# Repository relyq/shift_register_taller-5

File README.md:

# shift_register_taller-5

esquematica y diseño de pcb del proyecto de shift register de 5º año 2018<br>
./CAMOutputs/ - gerber shift register
./CAMOutputs-control/ - gerber control
./shift_register/ - directorio del proyecto de eagle con los .sch y .brd<br>
./docs/ - directorio con las datasheets<br>

el proyecto incluye un control para conectar a las entradas de un lado de la pcb y así controlar los registros sin necesidad de pulsadores en una protoboard

<h1>PDF</h1>
./shift_register.pdf - diseño de pcb principal<br>
./shift_register-control.pdf - diseño de pcb del control<br>
./shift_register-components.pdf - pcb principal lado componentes<br>
./shift_register-control-components.pdf - pcb del control lado componentes<br>
./shift_register-schematic.pdf - esquematica<br>
<br>
./shiftreg_imprimir.pdf - hoja con 4 copias de cada diseño de pcb para transferir por método de toner<br>
./shiftreg+control-colorinvert.pdf - hoja con 3 copias del diseño principal y 6 de cada control con colores invertidos para transferir por metodo de papel fotosensible UV<br>

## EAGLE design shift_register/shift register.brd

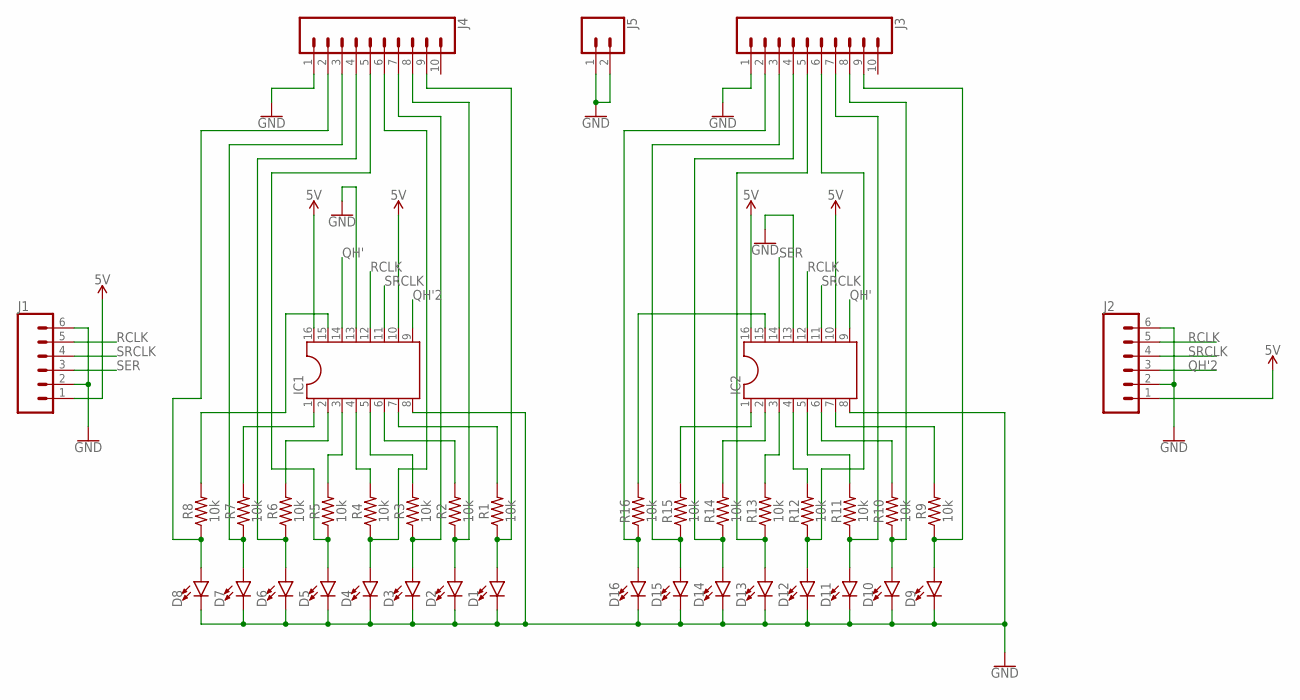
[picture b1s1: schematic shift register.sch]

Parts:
D1, D2, D3, D4, D5, D6, D7, D8, D9, D10, D11, D12, D13, D14, D15, D16: LED3MM; LED_3MM
IC1, IC2: DIL16
J1, J2: CONN_06SILK_FEMALE_PTH; 1X06
J3, J4: CONN_10"; 1X10
J5: CONN_02; 1X02
R1, R2, R3, R4, R5, R6, R7, R8, R9, R10, R11, R12, R13, R14, R15, R16: 10k; AXIAL-0.3

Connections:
5V: IC1.10, IC1.16, IC2.10, IC2.16, J1.1, J2.1
GND: D1.K (C), D2.K (C), D3.K (C), D4.K (C), D5.K (C), D6.K (C), D7.K (C), D8.K (C), D9.K (C), D10.K (C), D11.K (C), D12.K (C), D13.K (C), D14.K (C), D15.K (C), D16.K (C), IC1.8, IC1.13, IC2.8, IC2.13, J1.2, J1.6, J2.2, J2.6, J3.1, J4.1, J5.1, J5.2
unnamed: IC1.7, R1.P$2 (2)
unnamed: D9.A, J3.9, R9.P$1 (1)
unnamed: D7.A, J4.3, R7.P$1 (1)
unnamed: D6.A, J4.4, R6.P$1 (1)
unnamed: D5.A, J4.5, R5.P$1 (1)
unnamed: D4.A, J4.6, R4.P$1 (1)
unnamed: D3.A, J4.7, R3.P$1 (1)
unnamed: D2.A, J4.8, R2.P$1 (1)
unnamed: D10.A, J3.8, R10.P$1 (1)
unnamed: D11.A, J3.7, R11.P$1 (1)
unnamed: D12.A, J3.6, R12.P$1 (1)
unnamed: D13.A, J3.5, R13.P$1 (1)
unnamed: D14.A, J3.4, R14.P$1 (1)
unnamed: D15.A, J3.3, R15.P$1 (1)
unnamed: D16.A, J3.2, R16.P$1 (1)
unnamed: IC1.15, R8.P$2 (2)
unnamed: IC2.15, R16.P$2 (2)
unnamed: D8.A, J4.2, R8.P$1 (1)
unnamed: IC1.6, R2.P$2 (2)
unnamed: IC2.7, R9.P$2 (2)
unnamed: IC2.6, R10.P$2 (2)
unnamed: D1.A, J4.9, R1.P$1 (1)
unnamed: IC1.4, R4.P$2 (2)
unnamed: IC1.5, R3.P$2 (2)
unnamed: IC1.3, R5.P$2 (2)
unnamed: IC1.2, R6.P$2 (2)
unnamed: IC1.1, R7.P$2 (2)
unnamed: IC2.1, R15.P$2 (2)
unnamed: IC2.2, R14.P$2 (2)
unnamed: IC2.3, R13.P$2 (2)
unnamed: IC2.4, R12.P$2 (2)
unnamed: IC2.5, R11.P$2 (2)
QH': IC1.14, IC2.9
QH'2: IC1.9, J2.3
RCLK: IC1.12, IC2.12, J1.5, J2.5
SER: IC2.14, J1.3
SRCLK: IC1.11, IC2.11, J1.4, J2.4

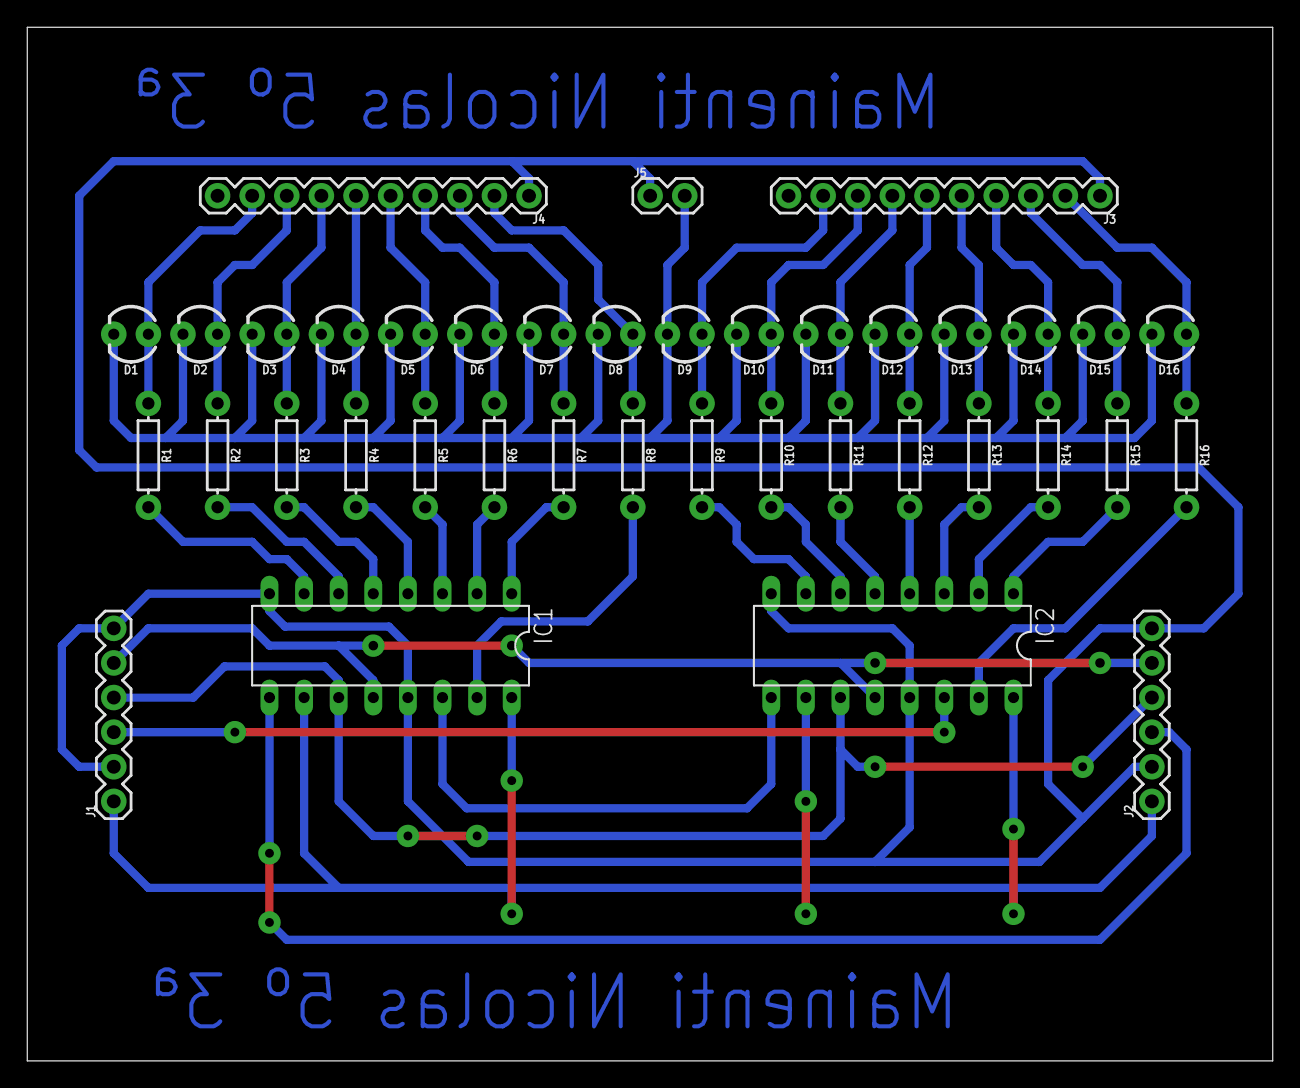
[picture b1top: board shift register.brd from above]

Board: 2 copper layers, 91.4 x 75.9 mm, 39 parts (0 on the bottom side), 39 nets.

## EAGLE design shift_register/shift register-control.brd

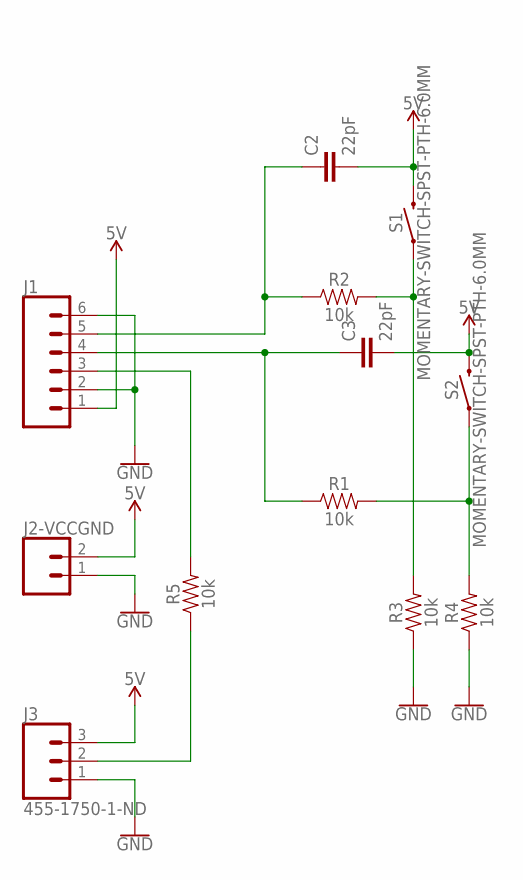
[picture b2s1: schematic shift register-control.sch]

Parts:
C2, C3: 22pF; CAP-PTH-2.54
J1: CONN_06SILK_FEMALE_PTH; 1X06
J2-VCCGND: CONN_02; 1X02
J3: 455-1750-1-ND; 1X03
R1, R2, R3, R4, R5: 10k; AXIAL-0.3
S1, S2: MOMENTARY-SWITCH-SPST-PTH-6.0MM; TACTILE_SWITCH_PTH_6.0MM

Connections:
5V: C2.2, C3.2, J1.1, J2-VCCGND.2, J3.3, S1.3 (2), S2.3 (2)
GND: J1.2, J1.6, J2-VCCGND.1, J3.1, R3.P$1 (1), R4.P$1 (1)
unnamed: J1.3, R5.P$2 (2)
unnamed: C3.1, J1.4, R1.P$1 (1)
unnamed: R2.P$2 (2), R3.P$2 (2), S1.1
unnamed: C2.1, J1.5, R2.P$1 (1)
unnamed: R1.P$2 (2), R4.P$2 (2), S2.1
unnamed: J3.2, R5.P$1 (1)

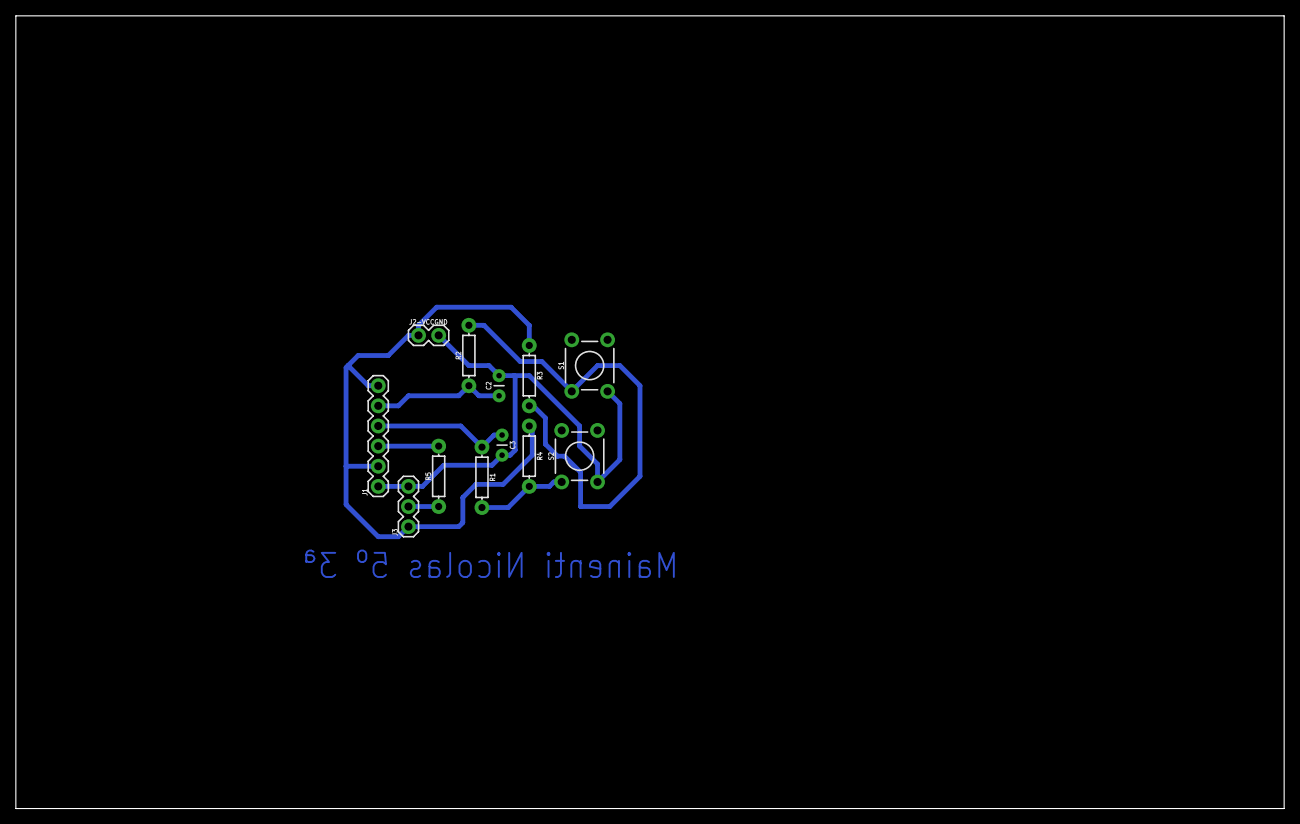
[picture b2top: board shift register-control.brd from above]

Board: 2 copper layers, 160.0 x 100.0 mm, 12 parts (0 on the bottom side), 8 nets.

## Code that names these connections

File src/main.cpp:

#include <Arduino.h>

const uint8_t SER = 8;
const uint8_t RCLK = 10;
const uint8_t SRCLK = 13;

void ser_set() { digitalWrite(SER, 1); }

void ser_clear() { digitalWrite(SER, 0); }

void srclk_pulse() {
  digitalWrite(SRCLK, 0);
  digitalWrite(SRCLK, 1);
}

void rclk_pulse() {
  digitalWrite(RCLK, 0);
  digitalWrite(RCLK, 1);
}

void rtol(bool b, int del);
void ltor(bool b, int del);

void setup() {
  pinMode(SER, OUTPUT);
  pinMode(RCLK, OUTPUT);
  pinMode(SRCLK, OUTPUT);
}

void loop() {
  int ms_del = 100;

  for (uint8_t j = 0; j < 4; j++) {
    ser_set();
    for (uint8_t i = 0; i < 4; i++) {
      srclk_pulse();
      rclk_pulse();
      delay(50);
    }

    ser_clear();
    for (uint8_t i = 0; i < 4; i++) {
      srclk_pulse();
      rclk_pulse();
      delay(50);
    }
  }

  for (uint8_t j = 0; j < 8; j++) {
    ser_set();
    for (uint8_t i = 0; i < 2; i++) {
      srclk_pulse();
      rclk_pulse();
      delay(50);
    }

    ser_clear();
    for (uint8_t i = 0; i < 2; i++) {
      srclk_pulse();
      rclk_pulse();
      delay(50);
    }
  }

  for (uint8_t j = 0; j < 16; j++) {
    ser_set();
    srclk_pulse();
    rclk_pulse();
    delay(50);

    ser_clear();
    srclk_pulse();
    rclk_pulse();
    delay(50);
  }

  for (uint8_t j = 0; j < 32; j++) {
    ser_set();
    for (uint8_t i = 0; i < 8; i++) {
      srclk_pulse();
    }
    rclk_pulse();
    delay(20);

    ser_clear();
    for (uint8_t i = 0; i < 8; i++) {
      srclk_pulse();
    }
    rclk_pulse();
    delay(20);
  }

  rtol(1, 20);
  delay(ms_del);
  rtol(0, 20);
  delay(ms_del);

  ltor(1, 20);
  delay(ms_del);
  ltor(0, 20);
  delay(ms_del);

  rtol(1, 20);
  delay(ms_del);
  ltor(0, 20);
  delay(ms_del);

  ltor(1, 20);
  delay(ms_del);
  rtol(0, 20);
  delay(ms_del);

  // no se que es esto pero esta bueno
  for (uint8_t i = 0; i < 16; i++) {
    ser_set();
    srclk_pulse();
    for (uint8_t j = 0; j < i - 1; j++) {
      ser_clear();
      srclk_pulse();
    }
    rclk_pulse();
    delay(100);
  }
  // tampoco se que es esto
  for (uint8_t i = 0; i < 16; i++) {
    ser_clear();
    for (uint8_t j = 15 - i; j < 16; j++) {
      srclk_pulse();
    }

    ser_set();
    for (uint8_t k = 0; k < 15 - i; k++) {
      srclk_pulse();
    }
    rclk_pulse();
    delay(100);
  }

  int microdel = 0;
  int milidelay = 16;

  while (1) {
    ser_set();
    srclk_pulse();
    rclk_pulse();
    if (microdel <= 16383) {
      delayMicroseconds(microdel);
      microdel += 1000;
    } else {
      delay(milidelay);
      milidelay = (milidelay + 10) * 1.41;
    }
    for (uint8_t i = 0; i < 15; i++) {
      ser_clear();
      srclk_pulse();

      rclk_pulse();
      if (microdel <= 16383)
        delayMicroseconds(microdel);
      else
        delay(milidelay);
    }
    for (uint8_t i = 1; i < 16; i++) {
      ser_clear();
      for (uint8_t j = 0; j < i + 1; j++) {
        srclk_pulse();
      }

      if (i == 15) break;

      ser_set();
      srclk_pulse();
      ser_clear();
      for (uint8_t k = 0; k < 15 - i; k++) {
        srclk_pulse();
      }
      rclk_pulse();
      if (microdel <= 16383)
        delayMicroseconds(microdel);
      else
        delay(milidelay);
    }

    if (milidelay >= 50) {
      milidelay = 16;
      microdel = 0;
    }
  }
}

void rtol(bool b, int del) {
  if (b) {
    ser_set();
    for (uint8_t i = 0; i < 16; i++) {
      srclk_pulse();
      rclk_pulse();
      delay(del);
    }
  } else {
    ser_clear();
    for (uint8_t i = 0; i < 16; i++) {
      srclk_pulse();
      rclk_pulse();
      delay(del);
    }
  }
}

void ltor(bool b, int del) {
  if (b) {
    for (uint8_t i = 0; i < 16; i++) {
      ser_set();
      for (uint8_t j = 0; j < i + 1; j++) {
        srclk_pulse();
      }

      ser_clear();
      for (uint8_t k = 0; k < 15 - i; k++) {
        srclk_pulse();
      }
      rclk_pulse();

      delay(del);
    }
  } else {
    for (uint8_t i = 0; i < 16; i++) {
      ser_clear();
      for (uint8_t j = 0; j < i + 1; j++) {
        srclk_pulse();
      }

      ser_set();
      for (uint8_t k = 0; k < 15 - i; k++) {
        srclk_pulse();
      }
      rclk_pulse();
      delay(del);
    }
  }
}

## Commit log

2020-08-19 firt commit
2020-08-24 diseño corregido
2020-08-24 gerber files
2020-11-25 updated control pcb
2020-11-27 copper pour en el control
2021-02-13 agregado programa de prueba
2021-02-13 programa de prueba actualizado
2021-07-13 esquematica pdf
2021-09-04 gerber
2021-10-27 informe de taller

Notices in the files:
parts and their libraries:
SparkFun-Connectors: Licensing: Creative Commons ShareAlike 4.0 International - https://creativecommons.org/licenses/by-sa/4.0
